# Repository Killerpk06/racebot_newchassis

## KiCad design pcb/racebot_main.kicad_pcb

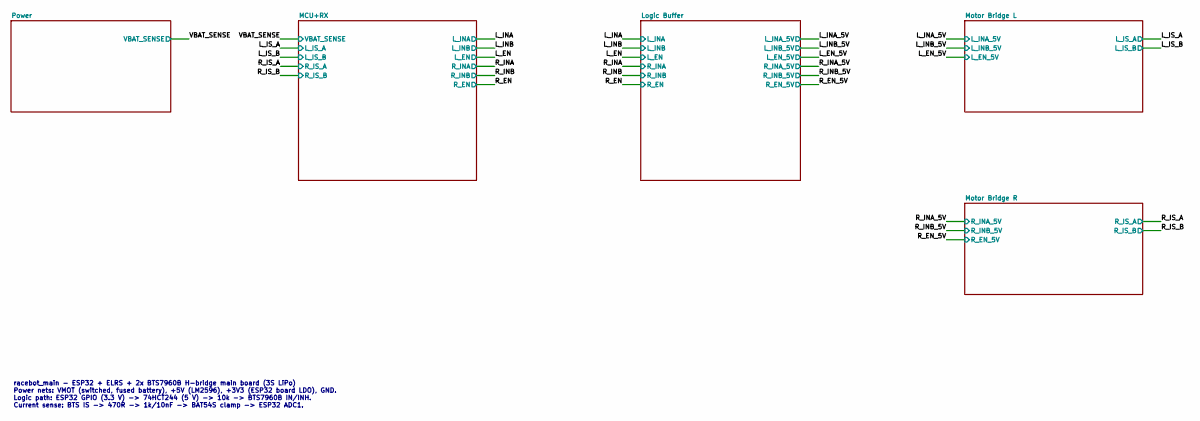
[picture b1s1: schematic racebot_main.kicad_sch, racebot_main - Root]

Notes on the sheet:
racebot_main - ESP32 + ELRS + 2x BTS7960B H-bridge main board (3S LiPo) Power nets: VMOT (switched, fused battery), +5V (LM2596), +3V3 (ESP32 board LDO), GND. Logic path: ESP32 GPIO (3.3 V) -> 74HCT244 (5 V) -> 10k -> BTS7960B IN/INH. Current sense: BTS IS -> 470R -> 1k/10nF -> BAT54S clamp -> ESP3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

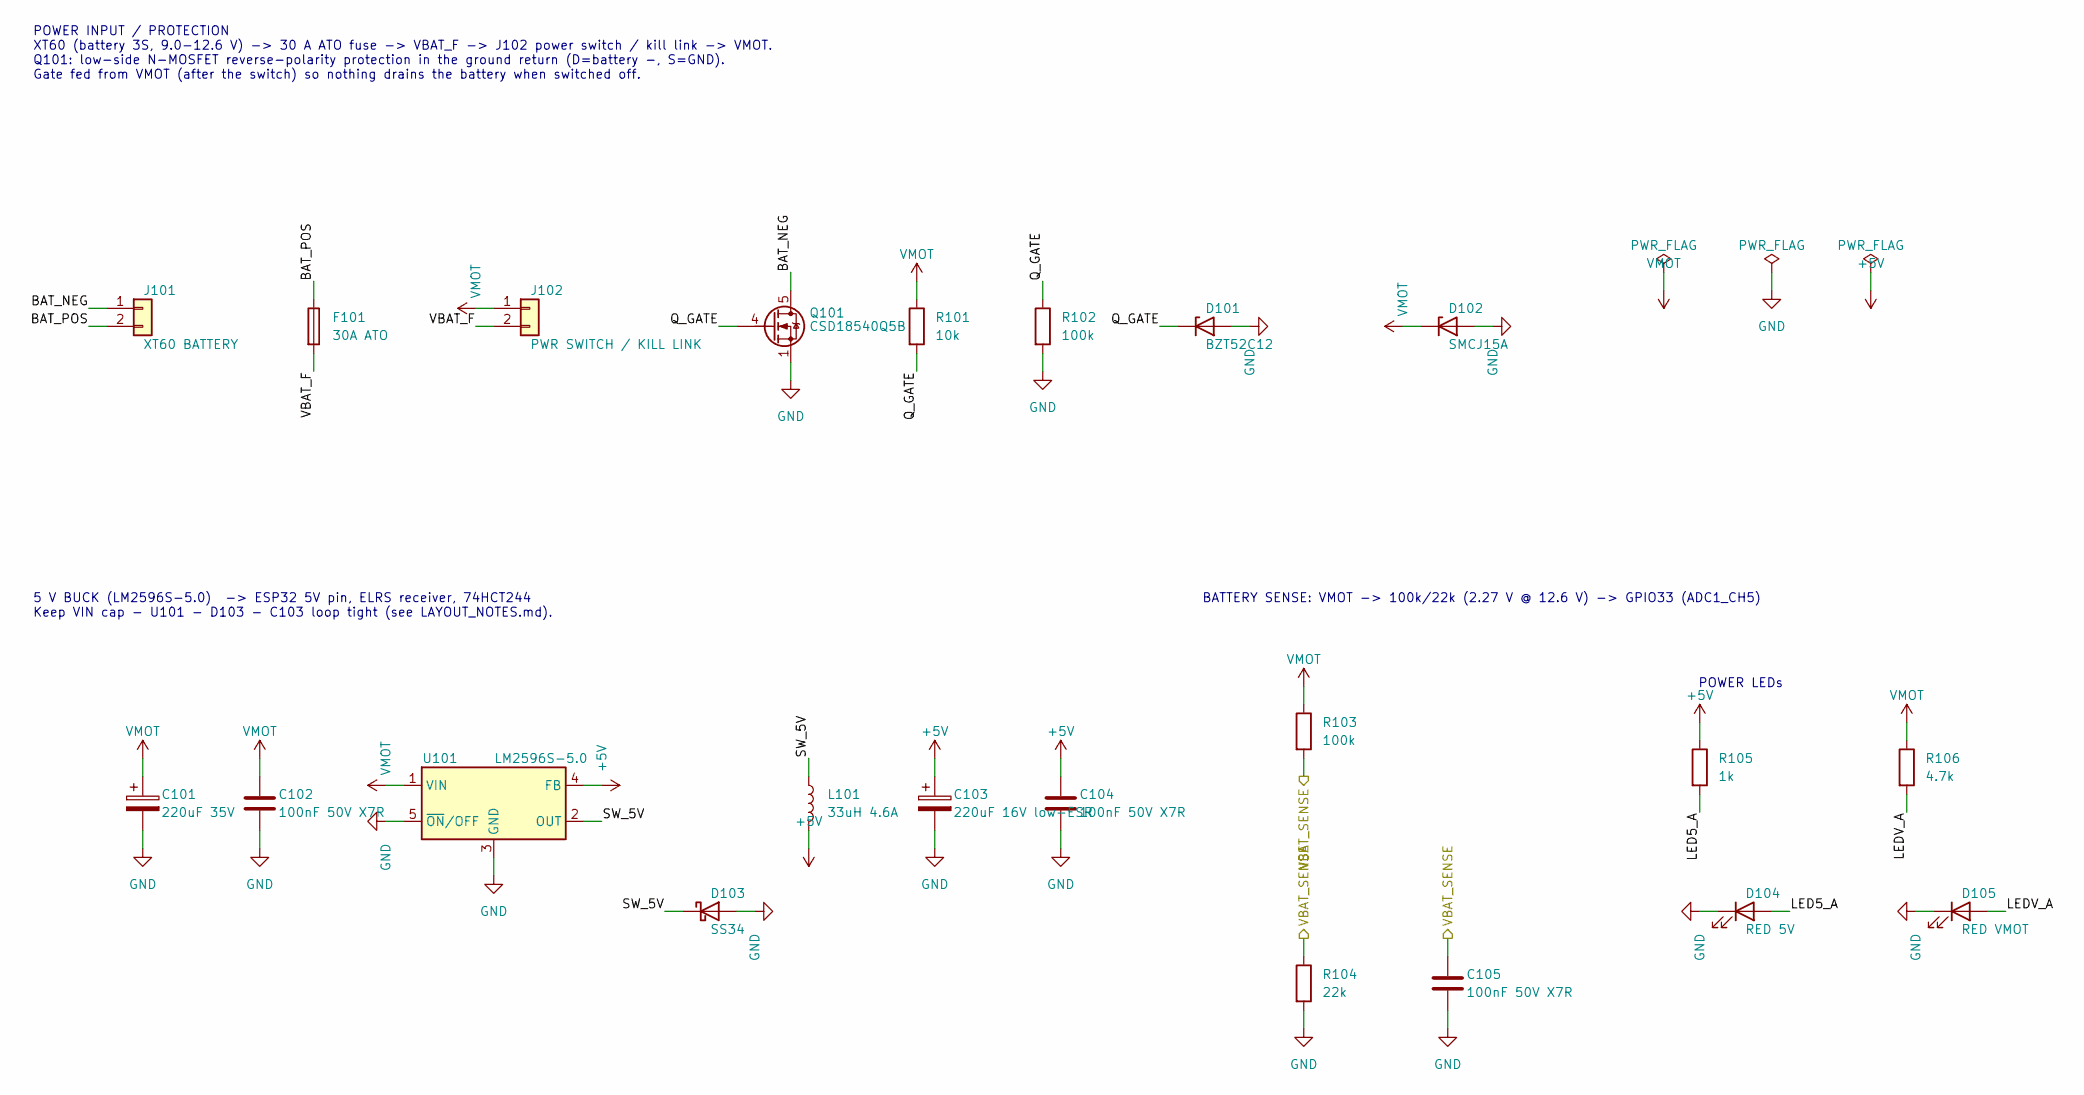
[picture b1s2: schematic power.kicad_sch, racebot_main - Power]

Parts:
C101: 220uF 35V; CP_Radial_D8.0mm_P3.50mm; MPN NXH35V220M8*11.5 3.5TP; LCSC C346959
C102, C104, C105: 100nF 50V X7R; C_0603_1608Metric; MPN CC0603KRX7R9BB104; LCSC C14663
C103: 220uF 16V low-ESR; CP_Radial_D6.3mm_P2.50mm; MPN 16YXJ220M6.3X11; LCSC C88757
D101: BZT52C12; D_SOD-123; MPN LBZT52C12T1G; LCSC C12747
D102: SMCJ15A; D_SMC; MPN SMCJ15A-13-F; LCSC C135138
D103: SS34; D_SMA; MPN SS34; LCSC C8678
D104: RED 5V; LED_0603_1608Metric; MPN KT-0603R; LCSC C2286
D105: RED VMOT; LED_0603_1608Metric; MPN KT-0603R; LCSC C2286
F101: 30A ATO; FuseHolder_Blade_ATO_Littelfuse_FLR_178.6165; MPN 178.6165.0002; LCSC C207061
J101: XT60 BATTERY; AMASS_XT60PW-M_1x02_P7.20mm_Horizontal; MPN XT60PW-M; LCSC C98732
J102: PWR SWITCH / KILL LINK; AMASS_XT60PW-F_1x02_P7.20mm_Horizontal; MPN XT60PW-F; LCSC C428722
L101: 33uH 4.6A; L_Bourns_SRR1260; MPN SRR1260-330M; LCSC C840528
Q101: CSD18540Q5B; TDSON-8-1; MPN CSD18540Q5B; LCSC C86513
R101: 10k; R_0603_1608Metric; MPN 0603WAF1002T5E; LCSC C25804
R102, R103: 100k; R_0603_1608Metric; MPN 0603WAF1003T5E; LCSC C25803
R104: 22k; R_0603_1608Metric; MPN 0603WAF2202T5E; LCSC C31850
R105: 1k; R_0603_1608Metric; MPN 0603WAF1001T5E; LCSC C21190
R106: 4.7k; R_0603_1608Metric; MPN 0603WAF4701T5E; LCSC C23162
U101: LM2596S-5.0; TO-263-5_TabPin3; MPN LM2596S-5.0/NOPB; LCSC C116713

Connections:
+5V: C103.1, C104.1, L101.2, R105.1, U101.4 (FB); also elsewhere on the board
/Power/BAT_NEG: J101.1, Q101.5 (D)
/Power/BAT_POS: F101.1, J101.2
/Power/LED5_A: D104.2 (A), R105.2
/Power/LEDV_A: D105.2 (A), R106.2
/Power/Q_GATE: D101.1 (K), Q101.4 (G), R101.2, R102.1
/Power/SW_5V: D103.1 (K), L101.1, U101.2 (OUT)
/Power/VBAT_F: F101.2, J102.2
/VBAT_SENSE: C105.1, R103.2, R104.1; also elsewhere on the board
GND: C101.2, C102.2, C103.2, C104.2, C105.2, D101.2 (A), D102.2 (A), D103.2 (A), D104.1 (K), D105.1 (K), Q101.1 (S), Q101.2 (S), Q101.3 (S), R102.2, R104.2, U101.3 (GND), U101.5 (~ON/OFF); also elsewhere on the board
VMOT: C101.1, C102.1, D102.1 (K), J102.1, R101.1, R103.1, R106.1, U101.1 (VIN); also elsewhere on the board

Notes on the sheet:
BATTERY SENSE: VMOT -> 100k/22k (2.27 V @ 12.6 V) -> GPIO33 (ADC1_CH5)
POWER LEDs
POWER INPUT / PROTECTION XT60 (battery 3S, 9.0-12.6 V) -> 30 A ATO fuse -> VBAT_F -> J102 power switch / kill link -> VMOT. Q101: low-side N-MOSFET reverse-polarity protection in the ground return (D=battery -, S=GND). Gate fed from VMOT (after the switch) so nothing drains the battery when switche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
5 V BUCK (LM2596S-5.0) -> ESP32 5V pin, ELRS receiver, 74HCT244 Keep VIN cap - U101 - D103 - C103 loop tight (see LAYOUT_NOTES.md).

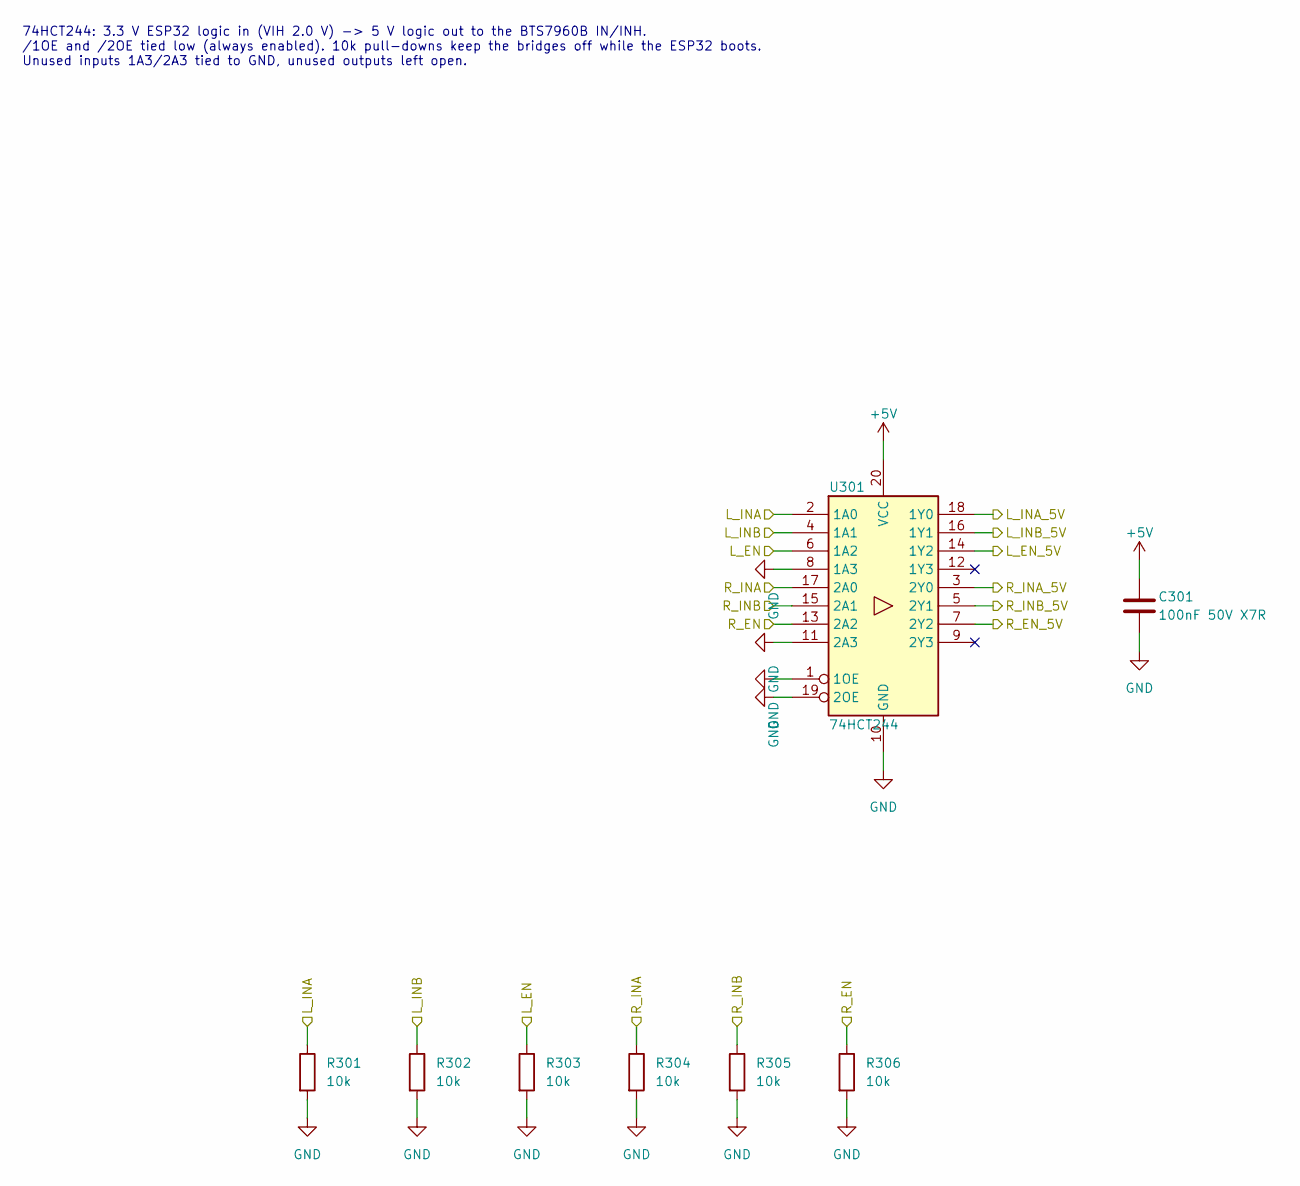
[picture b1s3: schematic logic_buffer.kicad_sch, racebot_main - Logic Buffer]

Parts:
C301: 100nF 50V X7R; C_0603_1608Metric; MPN CC0603KRX7R9BB104; LCSC C14663
R301, R302, R303, R304, R305, R306: 10k; R_0603_1608Metric; MPN 0603WAF1002T5E; LCSC C25804
U301: 74HCT244; SOIC-20W_7.5x12.8mm_P1.27mm; MPN 74HCT244D,653; LCSC C5978

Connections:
+5V: C301.1, U301.20 (VCC); also elsewhere on the board
/L_EN: R303.1, U301.6 (1A2); also elsewhere on the board
/L_EN_5V: U301.14 (1Y2); also elsewhere on the board
/L_INA: R301.1, U301.2 (1A0); also elsewhere on the board
/L_INA_5V: U301.18 (1Y0); also elsewhere on the board
/L_INB: R302.1, U301.4 (1A1); also elsewhere on the board
/L_INB_5V: U301.16 (1Y1); also elsewhere on the board
/R_EN: R306.1, U301.13 (2A2); also elsewhere on the board
/R_EN_5V: U301.7 (2Y2); also elsewhere on the board
/R_INA: R304.1, U301.17 (2A0); also elsewhere on the board
/R_INA_5V: U301.3 (2Y0); also elsewhere on the board
/R_INB: R305.1, U301.15 (2A1); also elsewhere on the board
/R_INB_5V: U301.5 (2Y1); also elsewhere on the board
GND: C301.2, R301.2, R302.2, R303.2, R304.2, R305.2, R306.2, U301.1 (1OE), U301.8 (1A3), U301.10 (GND), U301.11 (2A3), U301.19 (2OE); also elsewhere on the board

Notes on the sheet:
74HCT244: 3.3 V ESP32 logic in (VIH 2.0 V) -> 5 V logic out to the BTS7960B IN/INH. /1OE and /2OE tied low (always enabled). 10k pull-downs keep the bridges off while the ESP32 boots. Unused inputs 1A3/2A3 tied to GND, unused outputs left open.

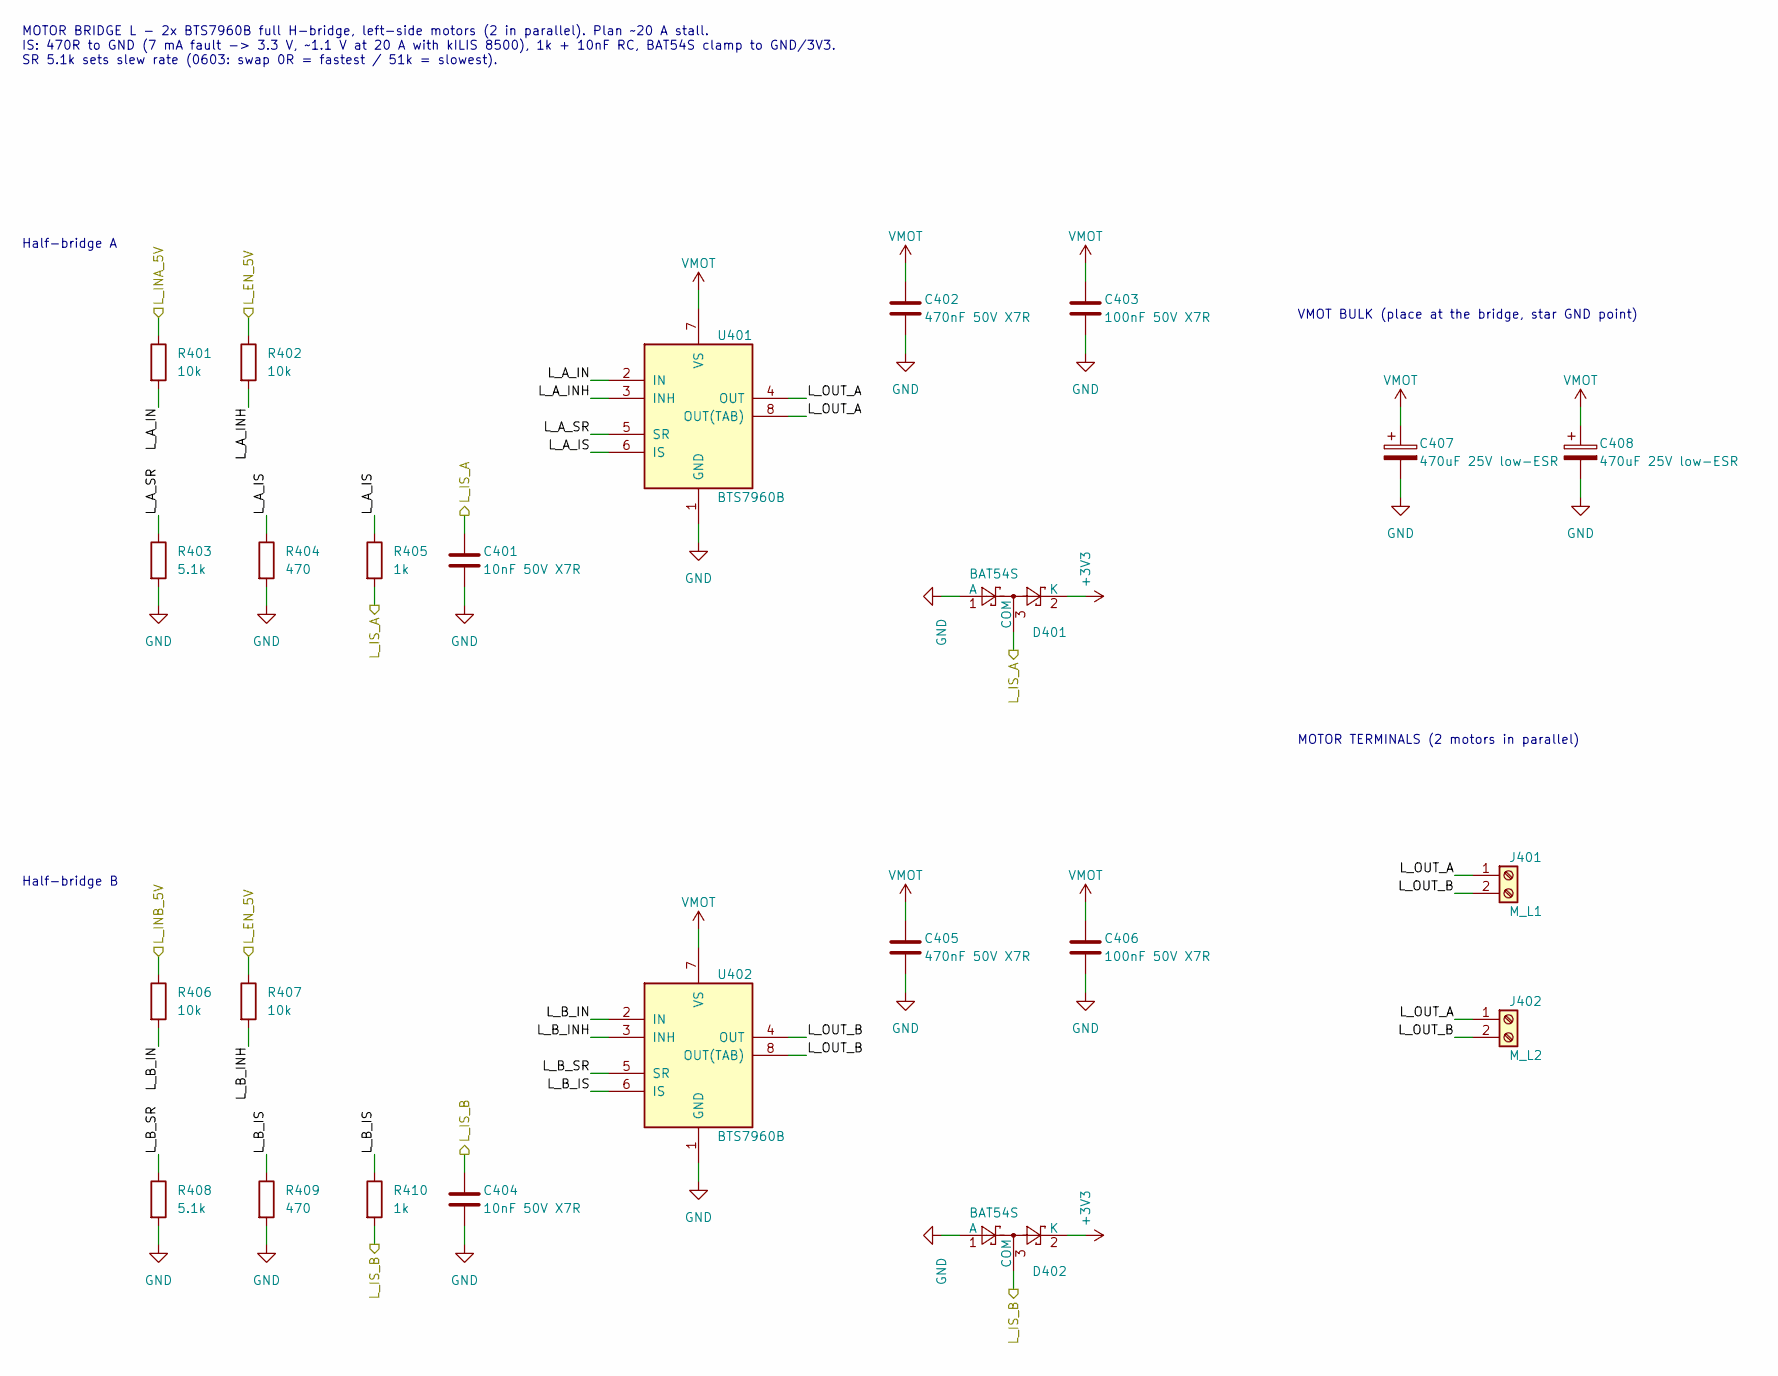
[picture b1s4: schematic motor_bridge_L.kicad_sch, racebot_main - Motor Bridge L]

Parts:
C401, C404: 10nF 50V X7R; C_0603_1608Metric; MPN 0603B103K500NT; LCSC C57112
C402, C405: 470nF 50V X7R; C_0805_2012Metric; MPN CL21B474KBFNNNE; LCSC C13967
C403, C406: 100nF 50V X7R; C_0603_1608Metric; MPN CC0603KRX7R9BB104; LCSC C14663
C407, C408: 470uF 25V low-ESR; CP_Radial_D10.0mm_P5.00mm; MPN GA25V470M10X12; LCSC C51018322
D401, D402: BAT54S; SOT-23; MPN BAT54S; LCSC C8592
J401: M_L1; TerminalBlock_Phoenix_MKDS-1,5-2-5.08_1x02_P5.08mm_Horizont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; MPN 1729128; LCSC C7509570
J402: M_L2; TerminalBlock_Phoenix_MKDS-1,5-2-5.08_1x02_P5.08mm_Horizont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; MPN 1729128; LCSC C7509570
R401, R402, R406, R407: 10k; R_0603_1608Metric; MPN 0603WAF1002T5E; LCSC C25804
R403, R408: 5.1k; R_0603_1608Metric; MPN 0603WAF5101T5E; LCSC C23186
R404, R409: 470; R_0603_1608Metric; MPN 0603WAF4700T5E; LCSC C23179
R405, R410: 1k; R_0603_1608Metric; MPN 0603WAF1001T5E; LCSC C21190
U401, U402: BTS7960B; TO-263-7_TabPin8; MPN BTS7960B; LCSC C5122776

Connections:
+3V3: D401.2 (K), D402.2 (K); also elsewhere on the board
/L_EN_5V: R402.1, R407.1; also elsewhere on the board
/L_INA_5V: R401.1; also elsewhere on the board
/L_INB_5V: R406.1; also elsewhere on the board
/L_IS_A: C401.1, D401.3 (COM), R405.2; also elsewhere on the board
/L_IS_B: C404.1, D402.3 (COM), R410.2; also elsewhere on the board
/Motor Bridge L/L_A_IN: R401.2, U401.2 (IN)
/Motor Bridge L/L_A_INH: R402.2, U401.3 (INH)
/Motor Bridge L/L_A_IS: R404.1, R405.1, U401.6 (IS)
/Motor Bridge L/L_A_SR: R403.1, U401.5 (SR)
/Motor Bridge L/L_B_IN: R406.2, U402.2 (IN)
/Motor Bridge L/L_B_INH: R407.2, U402.3 (INH)
/Motor Bridge L/L_B_IS: R409.1, R410.1, U402.6 (IS)
/Motor Bridge L/L_B_SR: R408.1, U402.5 (SR)
/Motor Bridge L/L_OUT_A: J401.1, J402.1, U401.4 (OUT), U401.8 (OUT(TAB))
/Motor Bridge L/L_OUT_B: J401.2, J402.2, U402.4 (OUT), U402.8 (OUT(TAB))
GND: C401.2, C402.2, C403.2, C404.2, C405.2, C406.2, C407.2, C408.2, D401.1 (A), D402.1 (A), R403.2, R404.2, R408.2, R409.2, U401.1 (GND), U402.1 (GND); also elsewhere on the board
VMOT: C402.1, C403.1, C405.1, C406.1, C407.1, C408.1, U401.7 (VS), U402.7 (VS); also elsewhere on the board

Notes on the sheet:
MOTOR BRIDGE L - 2x BTS7960B full H-bridge, left-side motors (2 in parallel). Plan ~20 A stall. IS: 470R to GND (7 mA fault -> 3.3 V, ~1.1 V at 20 A with kILIS 8500), 1k + 10nF RC, BAT54S clamp to GND/3V3. SR 5.1k sets slew rate (0603: swap 0R = fastest / 51k = slowest).
VMOT BULK (place at the bridge, star GND point)
MOTOR TERMINALS (2 motors in parallel)
Half-bridge A
Half-bridge B

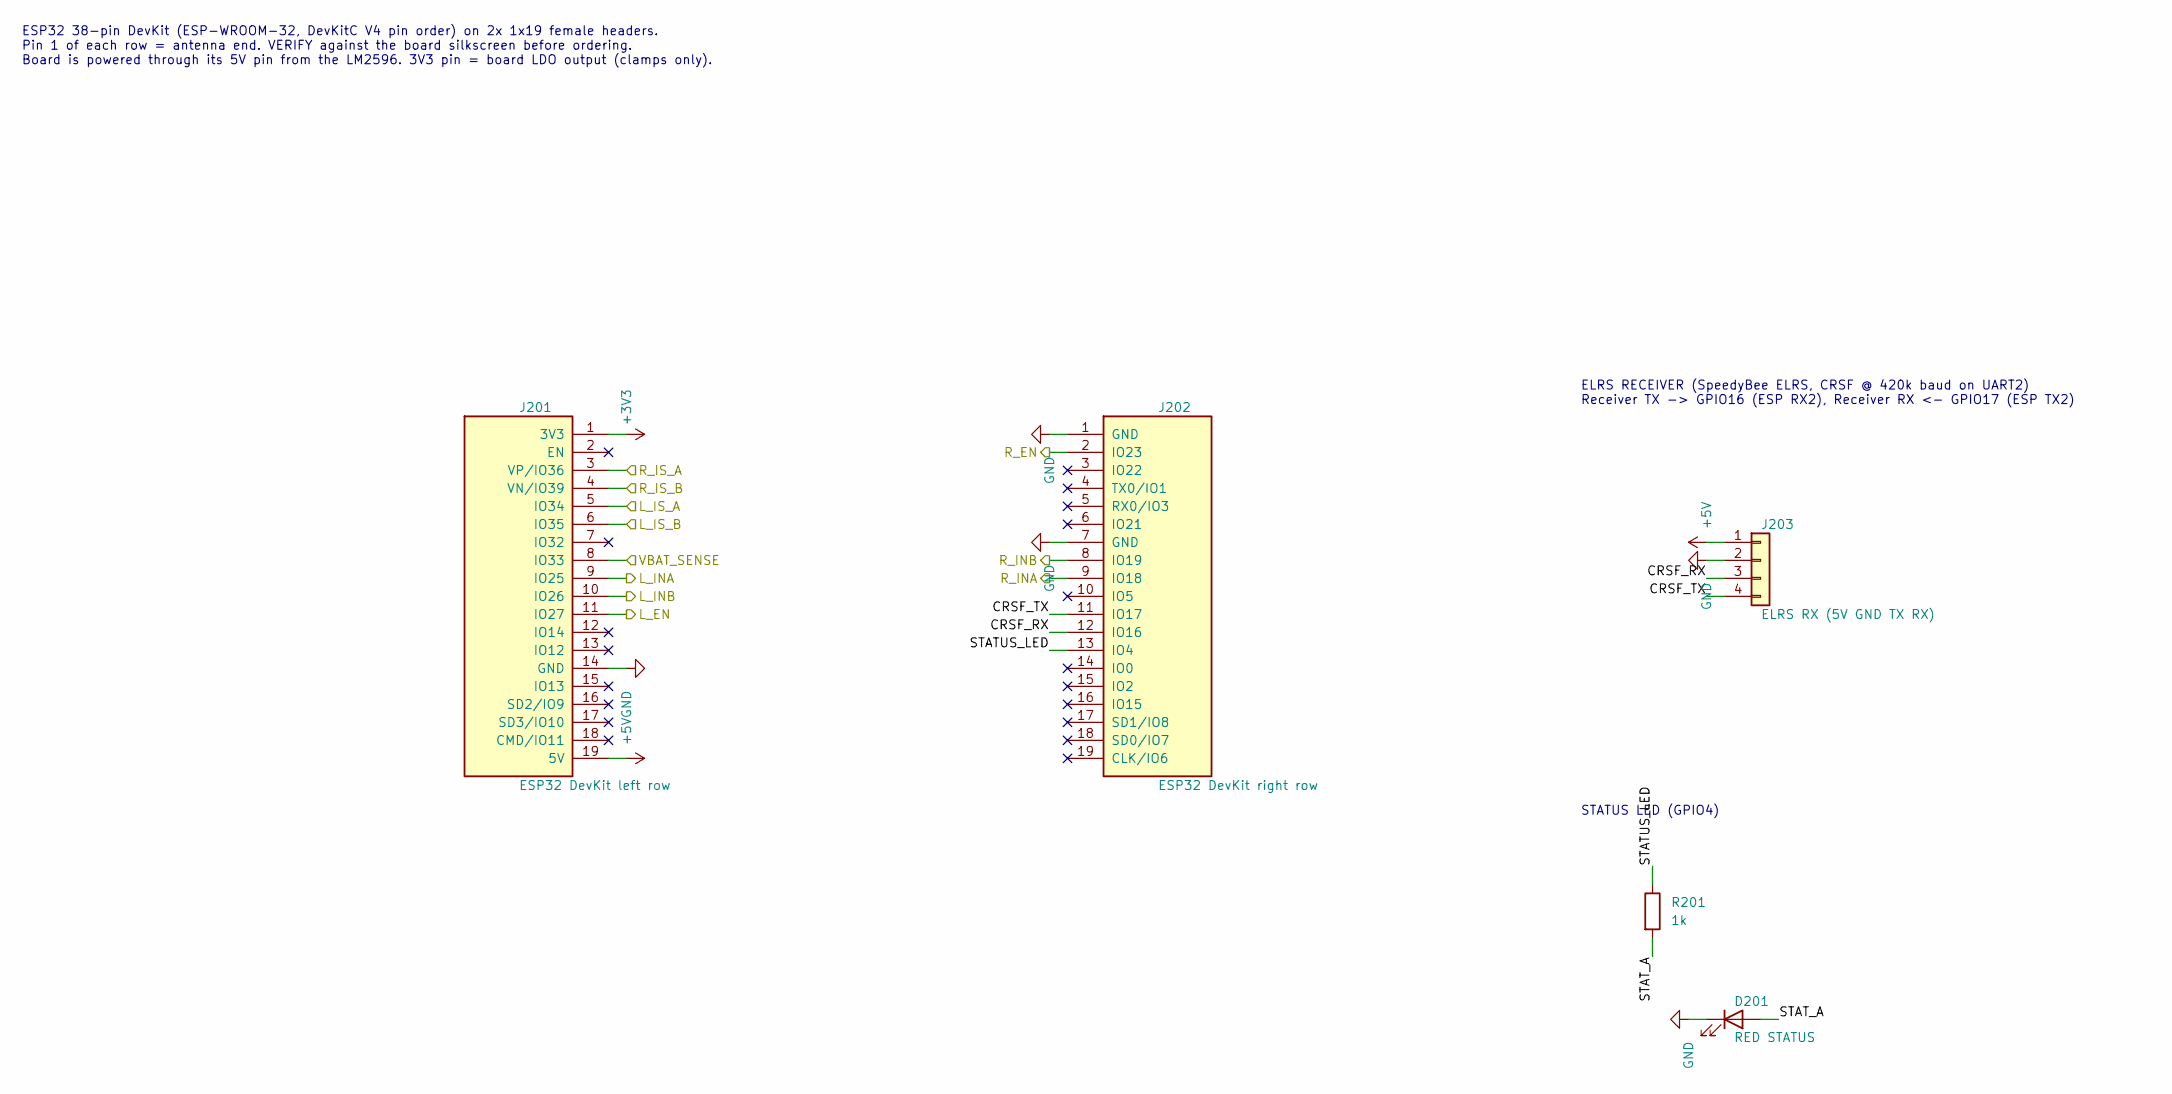
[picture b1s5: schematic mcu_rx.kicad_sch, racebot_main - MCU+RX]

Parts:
D201: RED STATUS; LED_0603_1608Metric; MPN KT-0603R; LCSC C2286
J201: ESP32 DevKit left row; PinSocket_1x19_P2.54mm_Vertical; MPN 2.54-1*19PFemale; LCSC C319202
J202: ESP32 DevKit right row; PinSocket_1x19_P2.54mm_Vertical; MPN 2.54-1*19PFemale; LCSC C319202
J203: ELRS RX (5V GND TX RX); PinHeader_1x04_P2.54mm_Vertical; MPN PZ254V-11-04P; LCSC C492403
R201: 1k; R_0603_1608Metric; MPN 0603WAF1001T5E; LCSC C21190

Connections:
+3V3: J201.1 (3V3); also elsewhere on the board
+5V: J201.19 (5V), J203.1; also elsewhere on the board
/L_EN: J201.11 (IO27); also elsewhere on the board
/L_INA: J201.9 (IO25); also elsewhere on the board
/L_INB: J201.10 (IO26); also elsewhere on the board
/L_IS_A: J201.5 (IO34); also elsewhere on the board
/L_IS_B: J201.6 (IO35); also elsewhere on the board
/MCU+RX/CRSF_RX: J202.12 (IO16), J203.3
/MCU+RX/CRSF_TX: J202.11 (IO17), J203.4
/MCU+RX/STATUS_LED: J202.13 (IO4), R201.1
/MCU+RX/STAT_A: D201.2 (A), R201.2
/R_EN: J202.2 (IO23); also elsewhere on the board
/R_INA: J202.9 (IO18); also elsewhere on the board
/R_INB: J202.8 (IO19); also elsewhere on the board
/R_IS_A: J201.3 (VP/IO36); also elsewhere on the board
/R_IS_B: J201.4 (VN/IO39); also elsewhere on the board
/VBAT_SENSE: J201.8 (IO33); also elsewhere on the board
GND: D201.1 (K), J201.14 (GND), J202.1 (GND), J202.7 (GND), J203.2; also elsewhere on the board

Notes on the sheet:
ELRS RECEIVER (SpeedyBee ELRS, CRSF @ 420k baud on UART2) Receiver TX -> GPIO16 (ESP RX2), Receiver RX <- GPIO17 (ESP TX2)
ESP32 38-pin DevKit (ESP-WROOM-32, DevKitC V4 pin order) on 2x 1x19 female headers. Pin 1 of each row = antenna end. VERIFY against the board silkscreen before ordering. Board is powered through its 5V pin from the LM2596. 3V3 pin = board LDO output (clamps only).
STATUS LED (GPIO4)

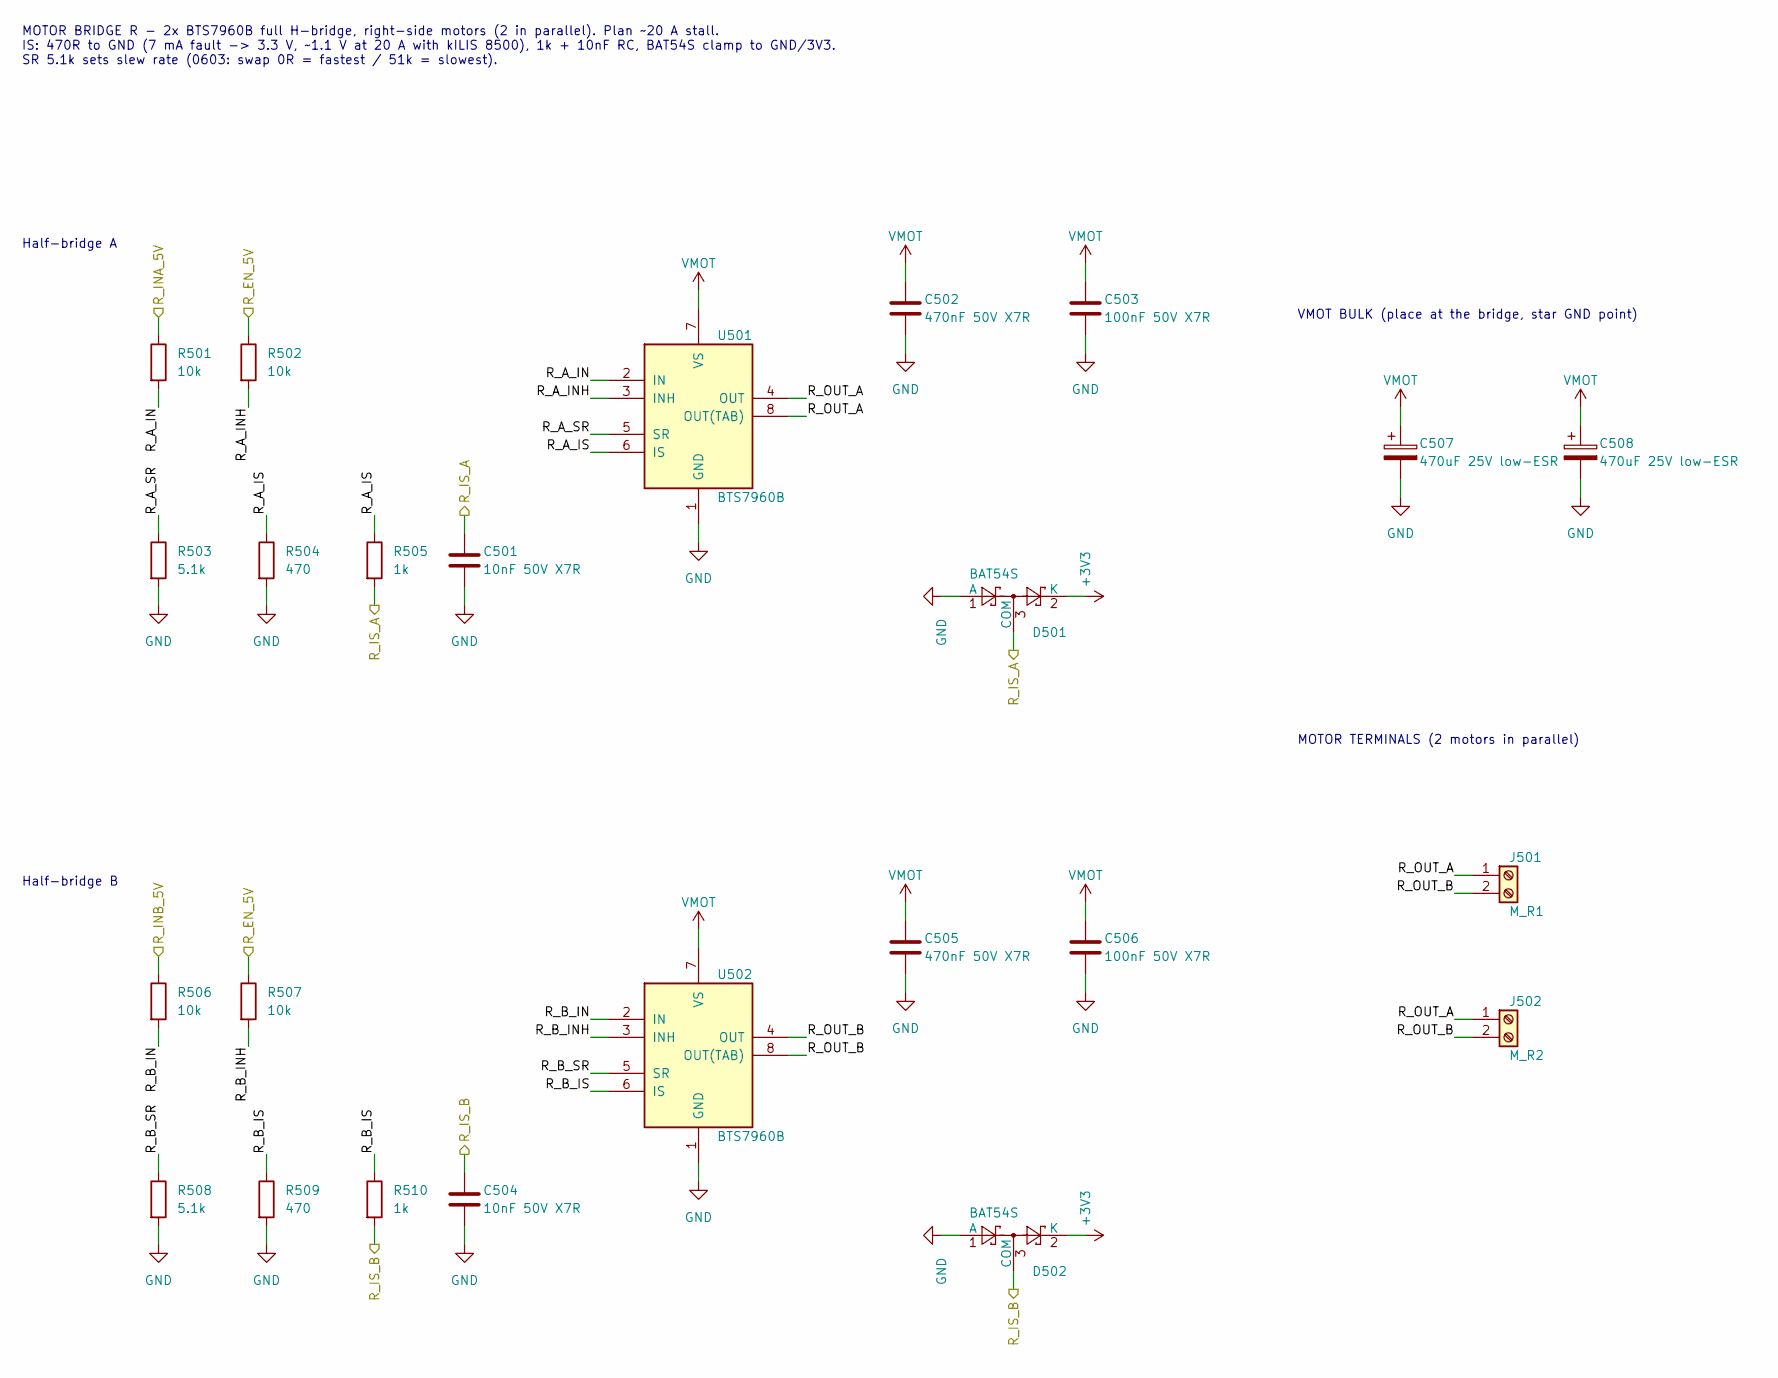
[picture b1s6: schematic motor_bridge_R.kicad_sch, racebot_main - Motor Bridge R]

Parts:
C501, C504: 10nF 50V X7R; C_0603_1608Metric; MPN 0603B103K500NT; LCSC C57112
C502, C505: 470nF 50V X7R; C_0805_2012Metric; MPN CL21B474KBFNNNE; LCSC C13967
C503, C506: 100nF 50V X7R; C_0603_1608Metric; MPN CC0603KRX7R9BB104; LCSC C14663
C507, C508: 470uF 25V low-ESR; CP_Radial_D10.0mm_P5.00mm; MPN GA25V470M10X12; LCSC C51018322
D501, D502: BAT54S; SOT-23; MPN BAT54S; LCSC C8592
J501: M_R1; TerminalBlock_Phoenix_MKDS-1,5-2-5.08_1x02_P5.08mm_Horizont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; MPN 1729128; LCSC C7509570
J502: M_R2; TerminalBlock_Phoenix_MKDS-1,5-2-5.08_1x02_P5.08mm_Horizont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; MPN 1729128; LCSC C7509570
R501, R502, R506, R507: 10k; R_0603_1608Metric; MPN 0603WAF1002T5E; LCSC C25804
R503, R508: 5.1k; R_0603_1608Metric; MPN 0603WAF5101T5E; LCSC C23186
R504, R509: 470; R_0603_1608Metric; MPN 0603WAF4700T5E; LCSC C23179
R505, R510: 1k; R_0603_1608Metric; MPN 0603WAF1001T5E; LCSC C21190
U501, U502: BTS7960B; TO-263-7_TabPin8; MPN BTS7960B; LCSC C5122776

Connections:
+3V3: D501.2 (K), D502.2 (K); also elsewhere on the board
/Motor Bridge R/R_A_IN: R501.2, U501.2 (IN)
/Motor Bridge R/R_A_INH: R502.2, U501.3 (INH)
/Motor Bridge R/R_A_IS: R504.1, R505.1, U501.6 (IS)
/Motor Bridge R/R_A_SR: R503.1, U501.5 (SR)
/Motor Bridge R/R_B_IN: R506.2, U502.2 (IN)
/Motor Bridge R/R_B_INH: R507.2, U502.3 (INH)
/Motor Bridge R/R_B_IS: R509.1, R510.1, U502.6 (IS)
/Motor Bridge R/R_B_SR: R508.1, U502.5 (SR)
/R_EN_5V: R502.1, R507.1; also elsewhere on the board
/R_INA_5V: R501.1; also elsewhere on the board
/R_INB_5V: R506.1; also elsewhere on the board
/R_IS_A: C501.1, D501.3 (COM), R505.2; also elsewhere on the board
/R_IS_B: C504.1, D502.3 (COM), R510.2; also elsewhere on the board
GND: C501.2, C502.2, C503.2, C504.2, C505.2, C506.2, C507.2, C508.2, D501.1 (A), D502.1 (A), R503.2, R504.2, R508.2, R509.2, U501.1 (GND), U502.1 (GND); also elsewhere on the board
VMOT: C502.1, C503.1, C505.1, C506.1, C507.1, C508.1, U501.7 (VS), U502.7 (VS); also elsewhere on the board

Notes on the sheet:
Half-bridge B
MOTOR TERMINALS (2 motors in parallel)
MOTOR BRIDGE R - 2x BTS7960B full H-bridge, right-side motors (2 in parallel). Plan ~20 A stall. IS: 470R to GND (7 mA fault -> 3.3 V, ~1.1 V at 20 A with kILIS 8500), 1k + 10nF RC, BAT54S clamp to GND/3V3. SR 5.1k sets slew rate (0603: swap 0R = fastest / 51k = slowest).
Half-bridge A
VMOT BULK (place at the bridge, star GND point)

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
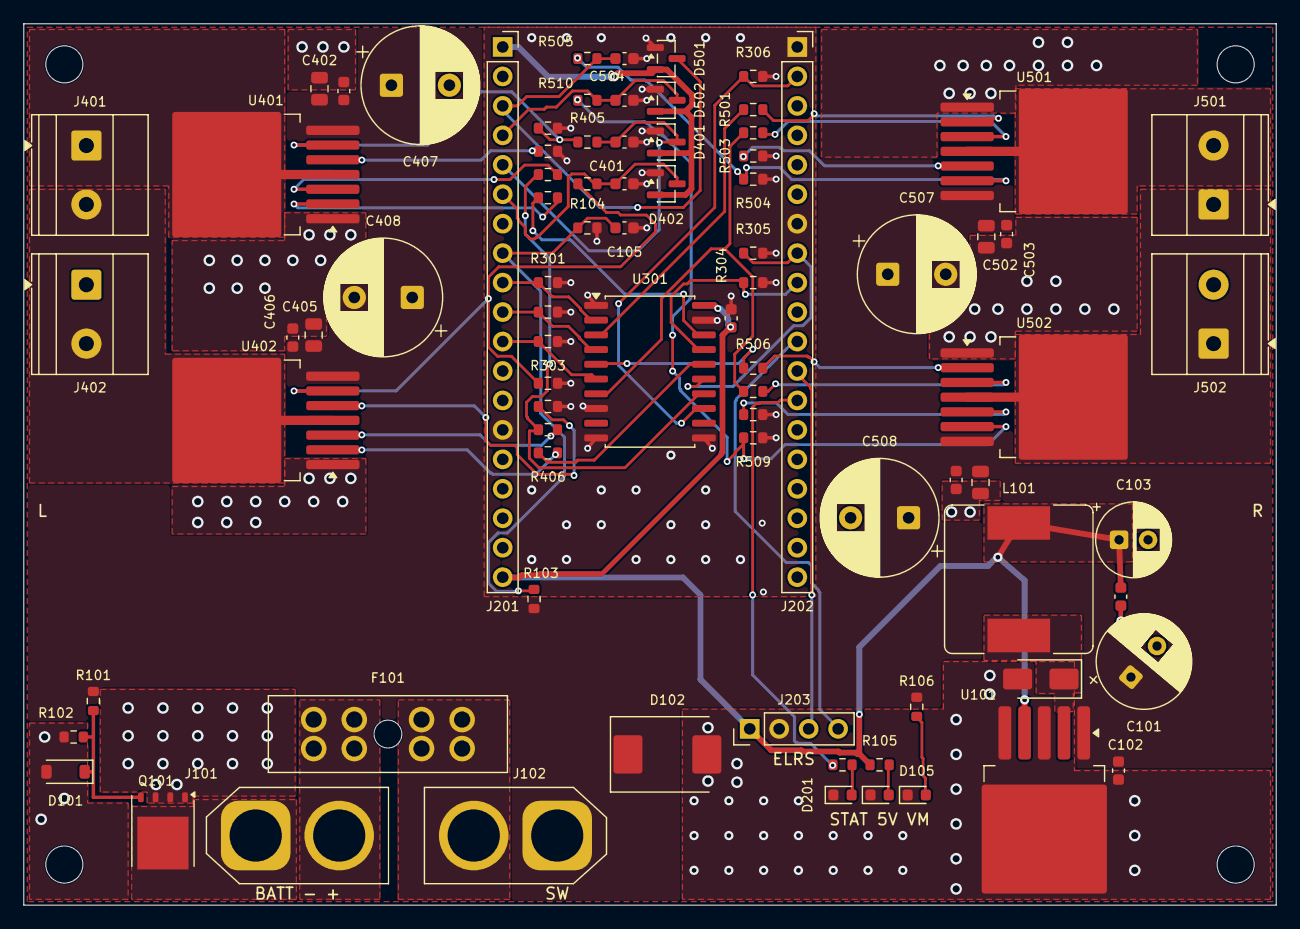
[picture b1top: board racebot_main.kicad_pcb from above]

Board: 2 copper layers, 108.0 x 76.0 mm, 87 parts (0 on the bottom side), 52 nets.

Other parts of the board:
H1, H2, H3, H4: M3; MountingHole_3.2mm_M3

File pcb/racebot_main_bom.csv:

"Designator","Value","Footprint","MPN","LCSC","Qty","Note"
"C101","220uF 35V","Capacitor_THT:CP_Radial_D8.0mm_P3.50mm","NXH35V220M8*11.5 3.5TP","C346959","1",""
"C102,C104,C105,C301,C403,C406,C503,C506","100nF 50V X7R","Capacitor_SMD:C_0603_1608Metric","CC0603KRX7R9BB104","C14663","8",""
"C103","220uF 16V low-ESR","Capacitor_THT:CP_Radial_D6.3mm_P2.50mm","16YXJ220M6.3X11","C88757","1",""
"C401,C404,C501,C504","10nF 50V X7R","Capacitor_SMD:C_0603_1608Metric","0603B103K500NT","C57112","4",""
"C402,C405,C502,C505","470nF 50V X7R","Capacitor_SMD:C_0805_2012Metric","CL21B474KBFNNNE","C13967","4",""
"C407,C408,C507,C508","470uF 25V low-ESR","Capacitor_THT:CP_Radial_D10.0mm_P5.00mm","GA25V470M10X12","C51018322","4",""
"D101","BZT52C12","Diode_SMD:D_SOD-123","LBZT52C12T1G","C12747","1",""
"D102","SMCJ15A","Diode_SMD:D_SMC","SMCJ15A-13-F","C135138","1","Unidirectional TVS 15 V standoff, clamps ~24.4 V"
"D103","SS34","Diode_SMD:D_SMA","SS34","C8678","1",""
"D104","RED 5V","LED_SMD:LED_0603_1608Metric","KT-0603R","C2286","1",""
"D105","RED VMOT","LED_SMD:LED_0603_1608Metric","KT-0603R","C2286","1",""
"D201","RED STATUS","LED_SMD:LED_0603_1608Metric","KT-0603R","C2286","1",""
"D401,D402,D501,D502","BAT54S","Package_TO_SOT_SMD:SOT-23","BAT54S","C8592","4",""
"F101","30A ATO","Fuse:FuseHolder_Blade_ATO_Littelfuse_FLR_178.6165","178.6165.0002","C207061","1","ATO holder; fit 30 A ATO blade fuse"
"J101","XT60 BATTERY","Connector_AMASS:AMASS_XT60-M_1x02_P7.20mm_Vertical","XT60PB-M.G.Y","C19268037","1","vertical; pin1 (bevelled end) = -, pin2 = +. Check against battery plug"
"J102","PWR SWITCH / KILL LINK","Connector_AMASS:AMASS_XT60-F_1x02_P7.20mm_Vertical","XT60PB-F.G.Y","C19268038","1","Plug a shorted XT60 link, or a >=30 A switch on an XT60 lead. See LAYOUT_NOTES.md"
"J201","ESP32 DevKit left row","Connector_PinSocket_2.54mm:PinSocket_1x19_P2.54mm_Vertical","2.54-1*19PFemale","C319202","1",""
"J202","ESP32 DevKit right row","Connector_PinSocket_2.54mm:PinSocket_1x19_P2.54mm_Vertical","2.54-1*19PFemale","C319202","1",""
"J203","ELRS RX (5V GND TX RX)","Connector_PinHeader_2.54mm:PinHeader_1x04_P2.54mm_Vertical","PZ254V-11-04P","C492403","1",""
"J401","M_L1","TerminalBlock_Phoenix:TerminalBlock_Phoenix_MKDS-1,5-2-5.08_1x02_P5.08mm_Horizontal","1729128","C7509570","1","front pad = L_OUT_A"
"J402","M_L2","TerminalBlock_Phoenix:TerminalBlock_Phoenix_MKDS-1,5-2-5.08_1x02_P5.08mm_Horizontal","1729128","C7509570","1","front pad = L_OUT_A"
"J501","M_R1","TerminalBlock_Phoenix:TerminalBlock_Phoenix_MKDS-1,5-2-5.08_1x02_P5.08mm_Horizontal","1729128","C7509570","1","front pad = R_OUT_A"
"J502","M_R2","TerminalBlock_Phoenix:TerminalBlock_Phoenix_MKDS-1,5-2-5.08_1x02_P5.08mm_Horizontal","1729128","C7509570","1","front pad = R_OUT_A"
"L101","33uH 4.6A","Inductor_SMD:L_Bourns_SRR1260","SRR1260-330M","C840528","1",""
"Q101","CSD18540Q5B","Package_TO_SOT_SMD:TDSON-8-1","CSD18540Q5B","C86513","1",""
"R101,R301,R302,R303,R304,R305,R306,R401,R402,R406,R407,R501,R502,R506,R507","10k","Resistor_SMD:R_0603_1608Metric","0603WAF1002T5E","C25804","15","IN series,INH series,boot pull-down"
"R102,R103","100k","Resistor_SMD:R_0603_1608Metric","0603WAF1003T5E","C25803","2",""
"R104","22k","Resistor_SMD:R_0603_1608Metric","0603WAF2202T5E","C31850","1",""
"R105,R201,R405,R410,R505,R510","1k","Resistor_SMD:R_0603_1608Metric","0603WAF1001T5E","C21190","6","IS RC filter"
"R106","4.7k","Resistor_SMD:R_0603_1608Metric","0603WAF4701T5E","C23162","1",""
"R403,R408,R503,R508","5.1k","Resistor_SMD:R_0603_1608Metric","0603WAF5101T5E","C23186","4","slew: fit 0R / 51k to tune"
"R404,R409,R504,R509","470","Resistor_SMD:R_0603_1608Metric","0603WAF4700T5E","C23179","4","IS load"
"U101","LM2596S-5.0","Package_TO_SOT_SMD:TO-263-5_TabPin3","LM2596S-5.0/NOPB","C116713","1",""
"U301","74HCT244","Package_SO:SOIC-20W_7.5x12.8mm_P1.27mm","74HCT244D,653","C5978","1",""
"U401,U402,U501,U502","BTS7960B","Package_TO_SOT_SMD:TO-263-7_TabPin8","BTS7960B","C5122776","4",""
